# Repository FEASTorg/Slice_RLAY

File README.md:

<div align="center">
  <!-- Title: -->
  
  <h2><a href="https://github.com/uwo-fast/Slice_RLAY"> Slice RLAY </a></h2>
  <!-- Labels: -->
  <!-- First row: -->

  <a href="https://certification.oshwa.org/">
    
    <!-- img src="https://img.shields.io/badge/OSHWA-Certified-darkgreen?style=flat-square" height="20" alt="OSHWA" -->       <!-- img src="https://img.shields.io/badge/OSHWA-Pending-darkorange?style=flat-square" height="20" alt="OSHWA" -->
  </a>

  <!-- Second row: -->
  <br>

  <!-- Short description: -->
  <h3>4-Channel Relay Slice for BREAD.</h3>
</div>

## Introduction
[Provide a brief introduction to the project, including the motivation and goals. Explain the significance and context of the research.]

## Project Overview
[Describe the project in more detail. This section can be split into subsections if necessary.]

## Installation
[Provide instructions for installing any necessary software or hardware components.]

## Usage
[Explain how to use the project. Include examples and screenshots if applicable.]

### Basic Usage
[Provide basic usage instructions.]

### Advanced Usage
[Provide advanced usage instructions, including any optional features or configurations.]

## Documentation
[Link to the detailed documentation if available. Provide instructions on how to access and navigate the documentation.]

## Contributing
[Explain how others can contribute to the project. Include guidelines for submitting issues, pull requests, and any coding standards.]

### Code of Conduct
[Link to the project's code of conduct if available.]

## License
[State the license under which the project is distributed. Include a link to the full license text.]

## Acknowledgements
[Acknowledge any contributors, collaborators, funding sources, or organizations that supported the project.]

## Contact
[Provide contact information for the project maintainer(s) or lead researcher(s). Include an email address or a link to a contact form.]

---

<div align="center">
  
</div>

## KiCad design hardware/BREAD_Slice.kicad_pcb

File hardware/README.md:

# Broadly Reconfigurable and Expandable Automation Device (BREAD) -- Slice Datasheet: **Relay** Slice (SLC-**RLAY**)

## Short Device Description

This device controls 4 relay channels via the Arduino, and receives
analog signals (optionally) as feedback.

## Quick Information

Device at a Glance

---

Short title Relay Slice
Part \# SLC-RLAY
Repository Link Link to OSF or other repository
Academic Paper DOI DOI link to published paper
Device Cost Monetary cost of the device
Assembly Difficulty Medium. Millable.
Application Area Controls, Power Monitoring

---

Device Connections

J2 -- Relay Output 1

---

Pin \# Description Rating
1 Normally closed switch of relay 277 VAC, 30V DC, 3A
2 Normally open switch of relay 277 VAC, 30V DC, 10A AC, 5A DC
3 Common pin N/A

---

J2 -- Relay Output 2

---

Pin \# Description Rating
1 Normally closed switch of relay 277 VAC, 30V DC, 3A
2 Normally open switch of relay 277 VAC, 30V DC, 10A AC, 5A DC
3 Common pin N/A

---

J2 -- Relay Output 3

---

Pin \# Description Rating
1 Normally closed switch of relay 277 VAC, 30V DC, 3A
2 Normally open switch of relay 277 VAC, 30V DC, 10A AC, 5A DC
3 Common pin N/A

---

J2 -- Relay Output 4

---

Pin \# Description Rating
1 Normally closed switch of relay 277 VAC, 30V DC, 3A
2 Normally open switch of relay 277 VAC, 30V DC, 10A AC, 5A DC
3 Common pin N/A

---

## Commands

---

**Write Switch(es) **(no significant returns)  
 **Byte**: Address **Bit**: 1 **Float: **Target Temp **Float: **Ramp Rate (d/m)
**Timed Write** (no significant returns)  
 **Byte**: Address **Bit**: 0 **Float: **0 **Float: **0
Analog Read (Returns selected voltages from analog feedback)

---

## Schematic

## Bill of Materials

---

Designator Description Quantity Cost / part URL
U1-4 Optocouplers 4 0.51 <https://www.digikey.com/short/5fmc702d>
RV1-4 10k Trimmer Potentiometer 4 4.16 <https://www.digikey.com/short/ftm98v7t>
R1-4 1k 1206 Packaging Resistor 4 0.1 <https://www.digikey.com/short/d1dmzmbb>
K1-4 G5Q1 SPDT Relay 4 1.52 <https://www.digikey.com/short/vj4jr0vq>
J6 01x04 1/10" Pitch Terminal Block 1 2.75 <https://www.digikey.com/short/rnm0hhhn>
J2-5 01x03 1/10" Pitch Terminal Block 4 2.06 <https://www.digikey.com/short/71d77cj2>
D5-8 5.1V Zener Diode 4 0.22 <https://www.digikey.com/short/tvbtwpmt>
D1-4 Standard THT Diode 4 0.21 <https://www.digikey.com/short/tp4mrn5q>
C1-2 10 µF 1206 Packaging Ceramic Capacitor 4 0.64 <https://www.digikey.com/short/2ffb0248>
A1 Arduino Nano 1 22.00 <https://www.digikey.com/en/products/detail/arduino/A000005/2638989>
J1 01x10 Female Header Pins 1 0.79 <https://www.digikey.com/short/23bfwwjh>

---

## Construction & Fabrication

List any tools that are required and short guide on the order which
parts should be soldered / assembled. Be sure to note any specialized
methods and point out components that may easily be soldered in the
incorrect orientation. Additionally include at least one picture of the
assembled board (include both sides if there are components on both
sides).

\[Image of the assembled Circuit Board\]

Fig #. Subtitle should go here.

## Configuration & Calibration

Include a list of default jumper and potentiometer positions:

Hardware Positions

- Turn P1 to be roughly 50%
- Turn P2 to be completely closed (turn clockwise until potentiometer
  clicks)
- Place a jumper to short out J3. Etc...

Detail any key parameters the end-user may want to adjust in the
firmware, and if there are any special instructions before programming
the Slice.

Tools Required For Calibration

- An oscilloscope with at least 15Mhz sampling
- A multimeter. Etc...

List all of the tools / instruments required for calibration. Provide a
detailed & step by step guide on how to calibrate (or validate) each
unique type of channel on the card. Include what variables in the
firmware may need to be adjusted (and when). Attach a wiring diagram for
each relevant calibration circuit.

\[Image of the calibration circuit\]

Fig #. Subtitle should go here.

## Usage & Constraints

List the relevant constraints for each type of channel on the card.
These parameters may be quantities like max current, max voltage,
frequency, sampling frequency, etc.

List an example wiring diagram of the slice in use, as well as some
suggested applications

\[Image of the example usage wiring diagram\]

Fig #. Subtitle should go here.

## General Comments on Slice

This section is intended as a catch-all for any topics that are relevant
to the Slice that don't fit in any other category.

## Revision Notes

- Rev 0 -- Initial document release (DATE HERE)

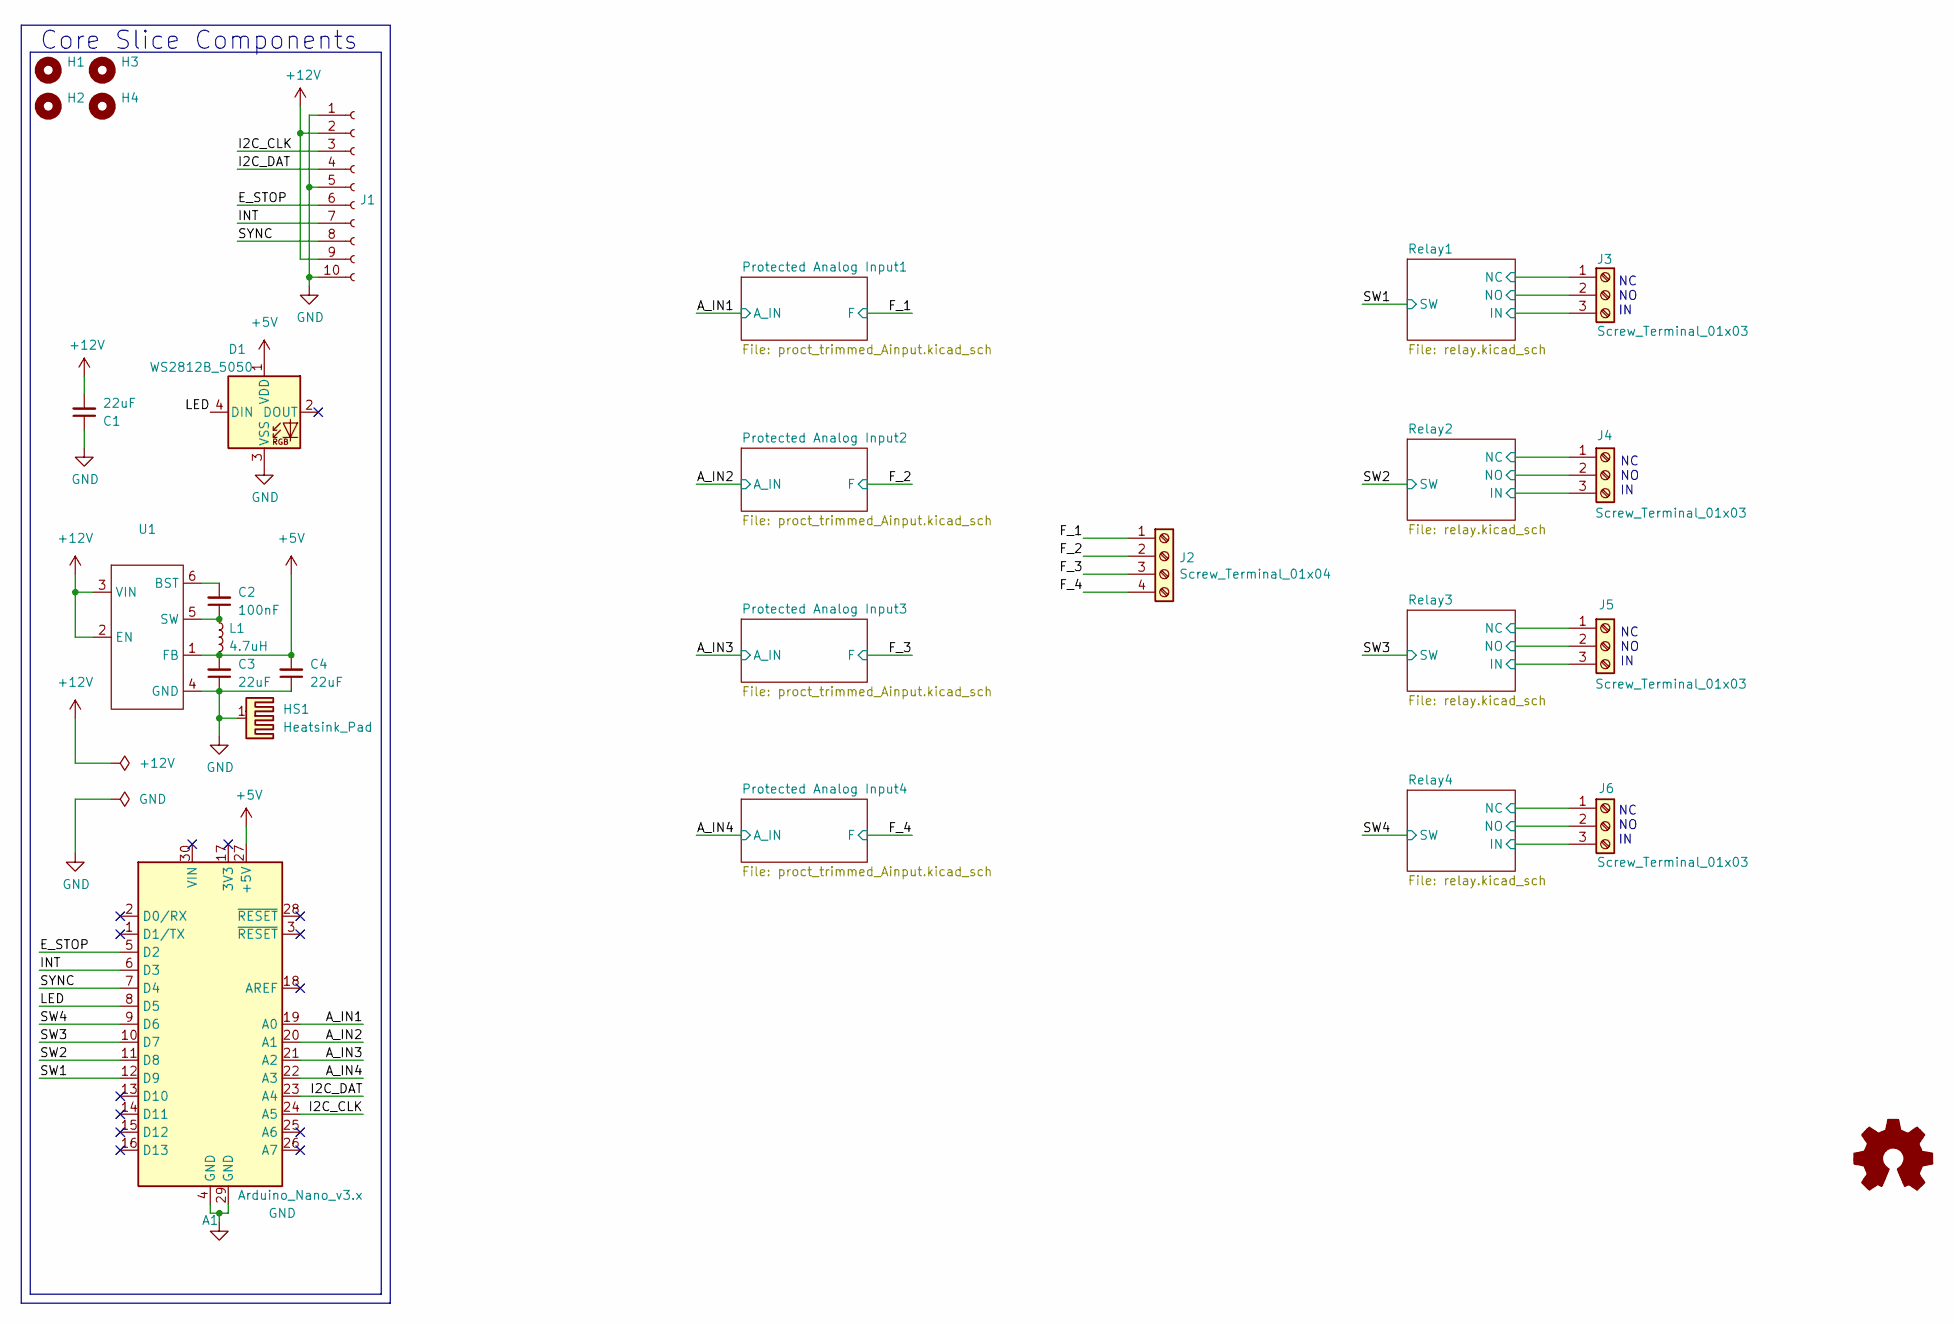
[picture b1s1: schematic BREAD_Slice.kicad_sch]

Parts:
A1: Arduino_Nano_v3.x; Arduino_Nano
C1, C3, C4: 22uF; C_1206_3216Metric
C2: 100nF; C_1206_3216Metric
D1: WS2812B_5050; WS2812-5050-4PIN
H1, H2, H3, H4: MountingHole; MountingHole_5mm
HS1: Heatsink_Pad; Thermal_Pad
J1: Conn_01x10_Female; PinSocket_1x10_P2.54mm_Horizontal
J2: Screw_Terminal_01x04; TerminalBlock_Phoenix_MPT-0,5-4-2.54_1x04_P2.54mm_Horizontal
J3, J4, J5, J6: Screw_Terminal_01x03; TerminalBlock_Phoenix_MKDS-1,5-3-5.08_1x03_P5.08mm_Horizont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
L1: 4.7uH; L_1210_3225Metric
U1: SOIC_05WU-7_DIO

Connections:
+5V: A1.27 (+5V), C3.2, C4.2, D1.1 (VDD), L1.2, U1.1 (FB); also elsewhere on the board
+12V: C1.2, J1.2, J1.9, U1.2 (EN), U1.3 (VIN)
/A_IN1: A1.19 (A0); also elsewhere on the board
/A_IN2: A1.20 (A1); also elsewhere on the board
/A_IN3: A1.21 (A2); also elsewhere on the board
/A_IN4: A1.22 (A3); also elsewhere on the board
/E_STOP: A1.5 (D2), J1.6
/F_1: J2.1; also elsewhere on the board
/F_2: J2.2; also elsewhere on the board
/F_3: J2.3; also elsewhere on the board
/F_4: J2.4; also elsewhere on the board
/I2C_CLK: A1.24 (A5), J1.3; also elsewhere on the board
/I2C_DAT: A1.23 (A4), J1.4; also elsewhere on the board
/INT: A1.6 (D3), J1.7
/LED: A1.8 (D5), D1.4 (DIN)
/Relay1/IN: J3.3; also elsewhere on the board
/Relay1/NC: J3.1; also elsewhere on the board
/Relay1/NO: J3.2; also elsewhere on the board
/Relay2/IN: J4.3; also elsewhere on the board
/Relay2/NC: J4.1; also elsewhere on the board
/Relay2/NO: J4.2; also elsewhere on the board
/Relay3/IN: J5.3; also elsewhere on the board
/Relay3/NC: J5.1; also elsewhere on the board
/Relay3/NO: J5.2; also elsewhere on the board
/Relay4/IN: J6.3; also elsewhere on the board
/Relay4/NC: J6.1; also elsewhere on the board
/Relay4/NO: J6.2; also elsewhere on the board
/SW1: A1.12 (D9); also elsewhere on the board
/SW2: A1.11 (D8); also elsewhere on the board
/SW3: A1.10 (D7); also elsewhere on the board
/SW4: A1.9 (D6); also elsewhere on the board
/SYNC: A1.7 (D4), J1.8
GND: A1.4 (GND), A1.29 (GND), C1.1, C3.1, C4.1, D1.3 (VSS), HS1.1, J1.1, J1.5, J1.10, U1.4 (GND); also elsewhere on the board
unnamed: C2.2, U1.6 (BST)
unnamed: C2.1, L1.1, U1.5 (SW)

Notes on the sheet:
NC NO IN
Core Slice Components

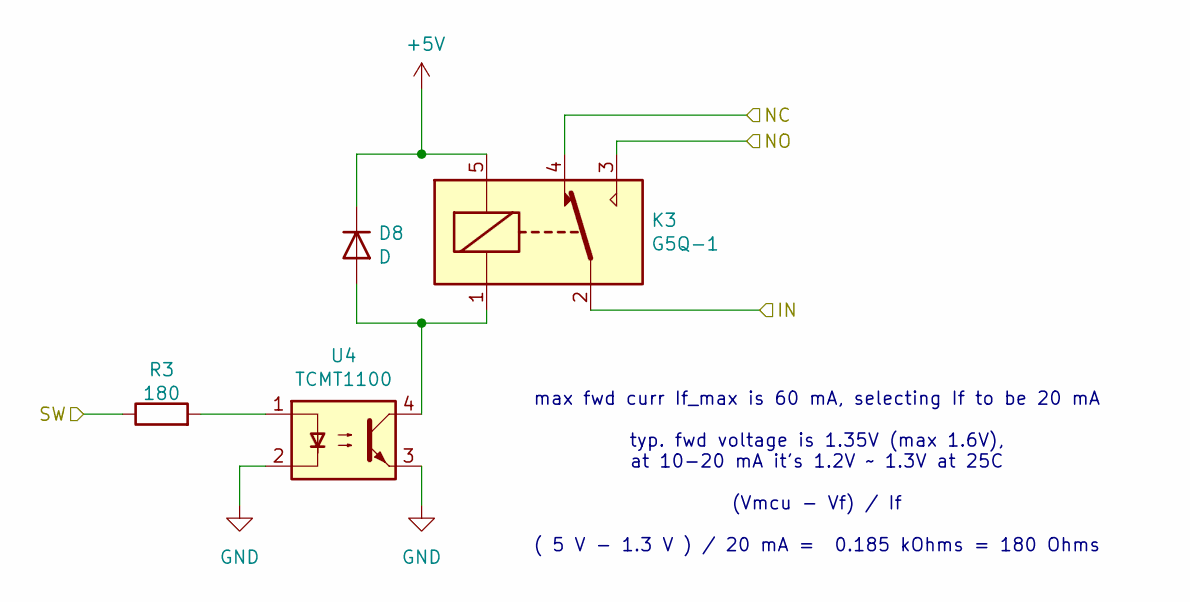
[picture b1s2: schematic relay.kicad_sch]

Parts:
D8: D; D_1206_3216Metric_Pad1.42x1.75mm_HandSolder
K3: G5Q-1; Relay_SPDT_Omron-G5Q-1
R3: 180; R_1206_3216Metric_Pad1.30x1.75mm_HandSolder
U4: TCMT1100; SOP-4_4.4x2.6mm_P1.27mm

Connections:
+5V: D8.1 (K), K3.5; also elsewhere on the board
/Relay3/IN: K3.2; also elsewhere on the board
/Relay3/NC: K3.4; also elsewhere on the board
/Relay3/NO: K3.3; also elsewhere on the board
/SW3: R3.1; also elsewhere on the board
GND: U4.2, U4.3; also elsewhere on the board
unnamed: D8.2 (A), K3.1, U4.4
unnamed: R3.2, U4.1

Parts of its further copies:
D6, D7, D9: D; D_1206_3216Metric_Pad1.42x1.75mm_HandSolder
K1, K2, K4: G5Q-1; Relay_SPDT_Omron-G5Q-1
R1, R2, R4: 180; R_1206_3216Metric_Pad1.30x1.75mm_HandSolder
U2, U3, U5: TCMT1100; SOP-4_4.4x2.6mm_P1.27mm

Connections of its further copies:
+5V: D6.1 (K), D7.1 (K), D9.1 (K), K1.5, K2.5, K4.5; also elsewhere on the board
/Relay1/IN: K1.2; also elsewhere on the board
/Relay1/NC: K1.4; also elsewhere on the board
/Relay1/NO: K1.3; also elsewhere on the board
/Relay2/IN: K2.2; also elsewhere on the board
/Relay2/NC: K2.4; also elsewhere on the board
/Relay2/NO: K2.3; also elsewhere on the board
/Relay4/IN: K4.2; also elsewhere on the board
/Relay4/NC: K4.4; also elsewhere on the board
/Relay4/NO: K4.3; also elsewhere on the board
/SW1: R1.1; also elsewhere on the board
/SW2: R2.1; also elsewhere on the board
/SW4: R4.1; also elsewhere on the board
GND: U2.2, U2.3, U3.2, U3.3, U5.2, U5.3; also elsewhere on the board
unnamed: D6.2 (A), K1.1, U2.4
unnamed: D7.2 (A), K2.1, U3.4
unnamed: D9.2 (A), K4.1, U5.4
unnamed: R1.2, U2.1
unnamed: R2.2, U3.1
unnamed: R4.2, U5.1

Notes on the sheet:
max fwd curr If_max is 60 mA, selecting If to be 20 mA typ. fwd voltage is 1.35V (max 1.6V), at 10-20 mA it's 1.2V ~ 1.3V at 25C (Vmcu - Vf) / If ( 5 V - 1.3 V ) / 20 mA = 0.185 kOhms = 180 Ohms

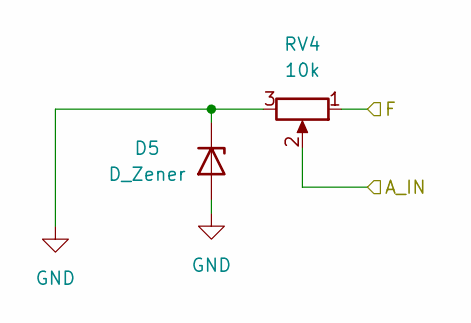
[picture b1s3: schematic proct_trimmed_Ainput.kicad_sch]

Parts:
D5: D_Zener; D_1206_3216Metric_Pad1.42x1.75mm_HandSolder
RV4: 10k; Potentiometer_Bourns_3266W_Vertical

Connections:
/A_IN4: RV4.2; also elsewhere on the board
/F_4: RV4.1; also elsewhere on the board
GND: D5.1 (K), D5.2 (A), RV4.3; also elsewhere on the board

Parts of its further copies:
D2, D3, D4: D_Zener; D_1206_3216Metric_Pad1.42x1.75mm_HandSolder
RV1, RV2, RV3: 10k; Potentiometer_Bourns_3266W_Vertical

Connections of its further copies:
/A_IN1: RV1.2; also elsewhere on the board
/A_IN2: RV2.2; also elsewhere on the board
/A_IN3: RV3.2; also elsewhere on the board
/F_1: RV1.1; also elsewhere on the board
/F_2: RV2.1; also elsewhere on the board
/F_3: RV3.1; also elsewhere on the board
GND: D2.1 (K), D2.2 (A), D3.1 (K), D3.2 (A), D4.1 (K), D4.2 (A), RV1.3, RV2.3, RV3.3; also elsewhere on the board

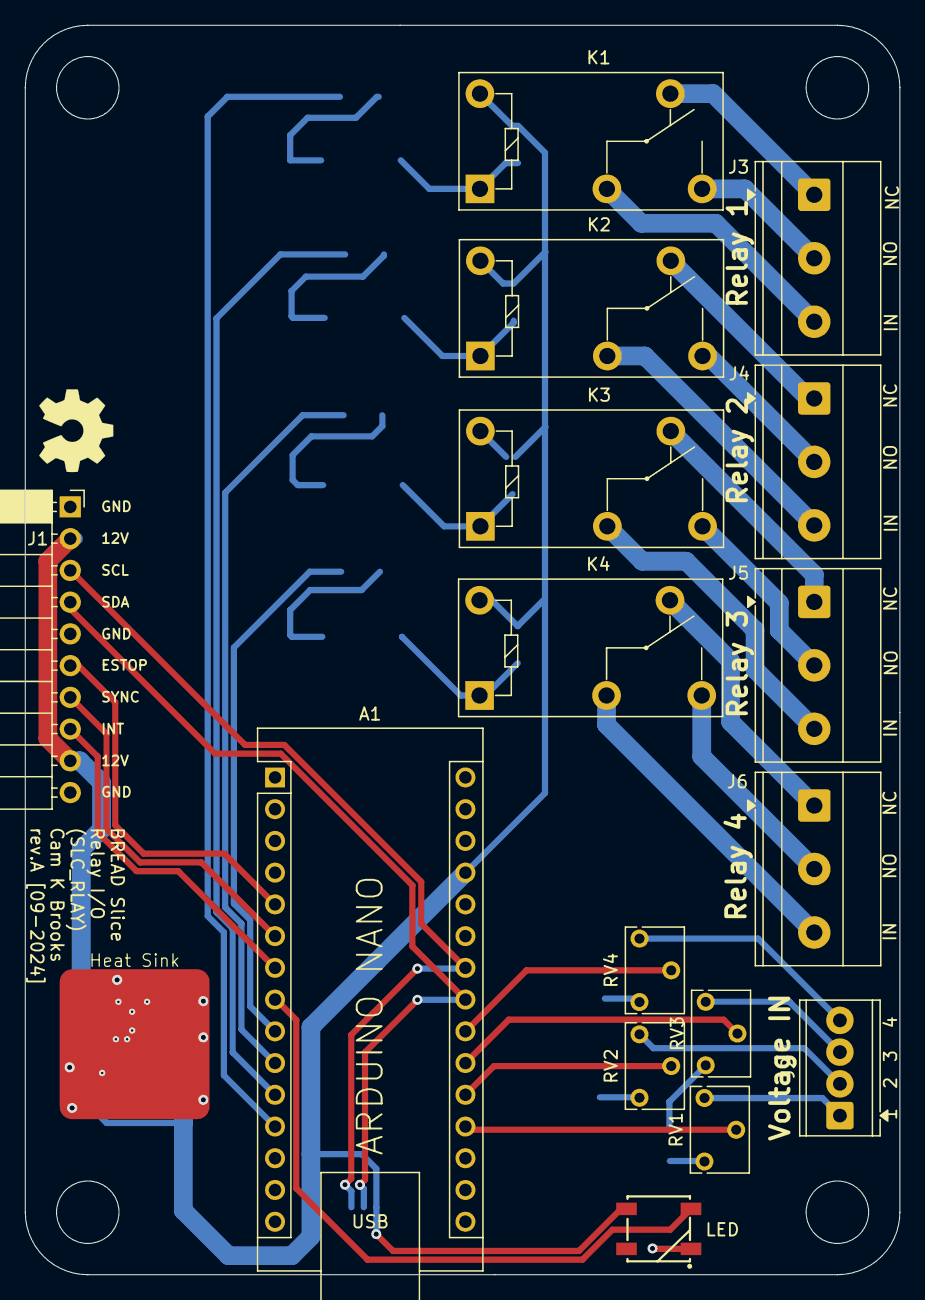
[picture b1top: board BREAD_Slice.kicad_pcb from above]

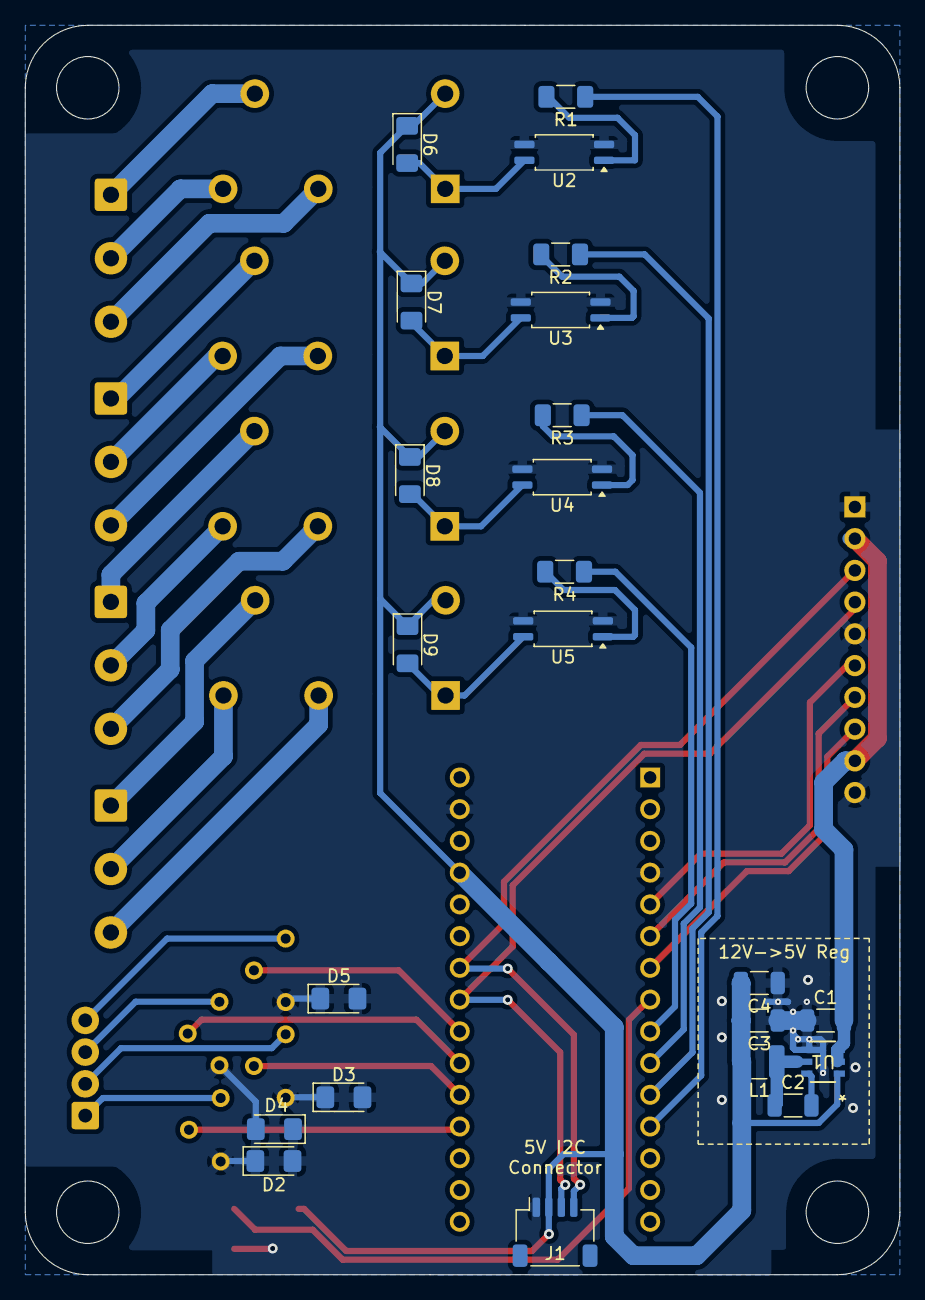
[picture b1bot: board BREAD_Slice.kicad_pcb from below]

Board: 2 copper layers, 70.0 x 100.0 mm, 45 parts (23 on the bottom side), 43 nets.

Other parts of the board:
J1#2: I2C_01x04; JST_SH_SM04B-SRSS-TB_1x04-1MP_P1.00mm_Horizontal
Logo1: Logo_Open_Hardware_Small; OSHW-Symbol_6.7x6mm_SilkScreen

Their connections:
+5V: J1#2.2; also elsewhere on the board
/I2C_CLK: J1#2.4; also elsewhere on the board
/I2C_DAT: J1#2.3; also elsewhere on the board
GND: J1#2.1; also elsewhere on the board

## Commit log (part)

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2024-08-16 added firmware and the updated PCB with new BREAD format
2024-09-12 fixed current limiting resistor on optocoupler input
2024-09-12 changed terminals to meet those of the relays max output with margin
2024-09-30 JLCPCB order rev-A
2025-10-20 add test script and debug pcb issues with digital line resistor values
2026-02-10 update to use latest kmlib; needs revision for connectors and ground inputs on analog inputs
2026-02-11 add connector blocks to parts doc
2026-05-20 Add slice.yaml manifest (schema v1.0)
2026-05-24 Add KiBot/docs pipeline
2026-05-24 📄 KiBot index + board renders (auto)
2026-05-24 TODO: all CI green
2026-05-24 Standardize TODO.md with Pass 1/Pass 2 structure
